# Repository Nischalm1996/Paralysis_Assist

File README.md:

# Paralysis_Assist

## Pin Connection from Board 
| Pin Name  | Digital Pin                            |
|-----------|----------------------------------------|
| CS_SDCARD | D2                                     |
| SOUND_D0  | D3  *Mic sensor from paralysed person* |
| AUDIO_OUT | D4 *to speaker*                        |
| MISO      | D5                                     |
| MOSI      | D10                                    |
| OK        | D6                                     |
| LEFT      | D7                                     |
| RIGHT     | D9                                     |
| BACK      | D8                                     |
| RIGHT     | D9                                     |
| CS_DISP   | D11                                    |
| RST       | D12                                    |
| TEMP      | A3                                     |
| RED       | A2                                     |
| GREEN     | A1                                     |
| BLUE      | A0                                     |

### MODULES USED
- DISPLAY 12864 SPI CONNECTOR
- NODE MCU
- MIC SENSOR
- MPU6050 ACCELOROMETER
- SD CARD
- LM35
- NAVIGATION BUTTON
- SOUND OUT----LM386
- RGB LED

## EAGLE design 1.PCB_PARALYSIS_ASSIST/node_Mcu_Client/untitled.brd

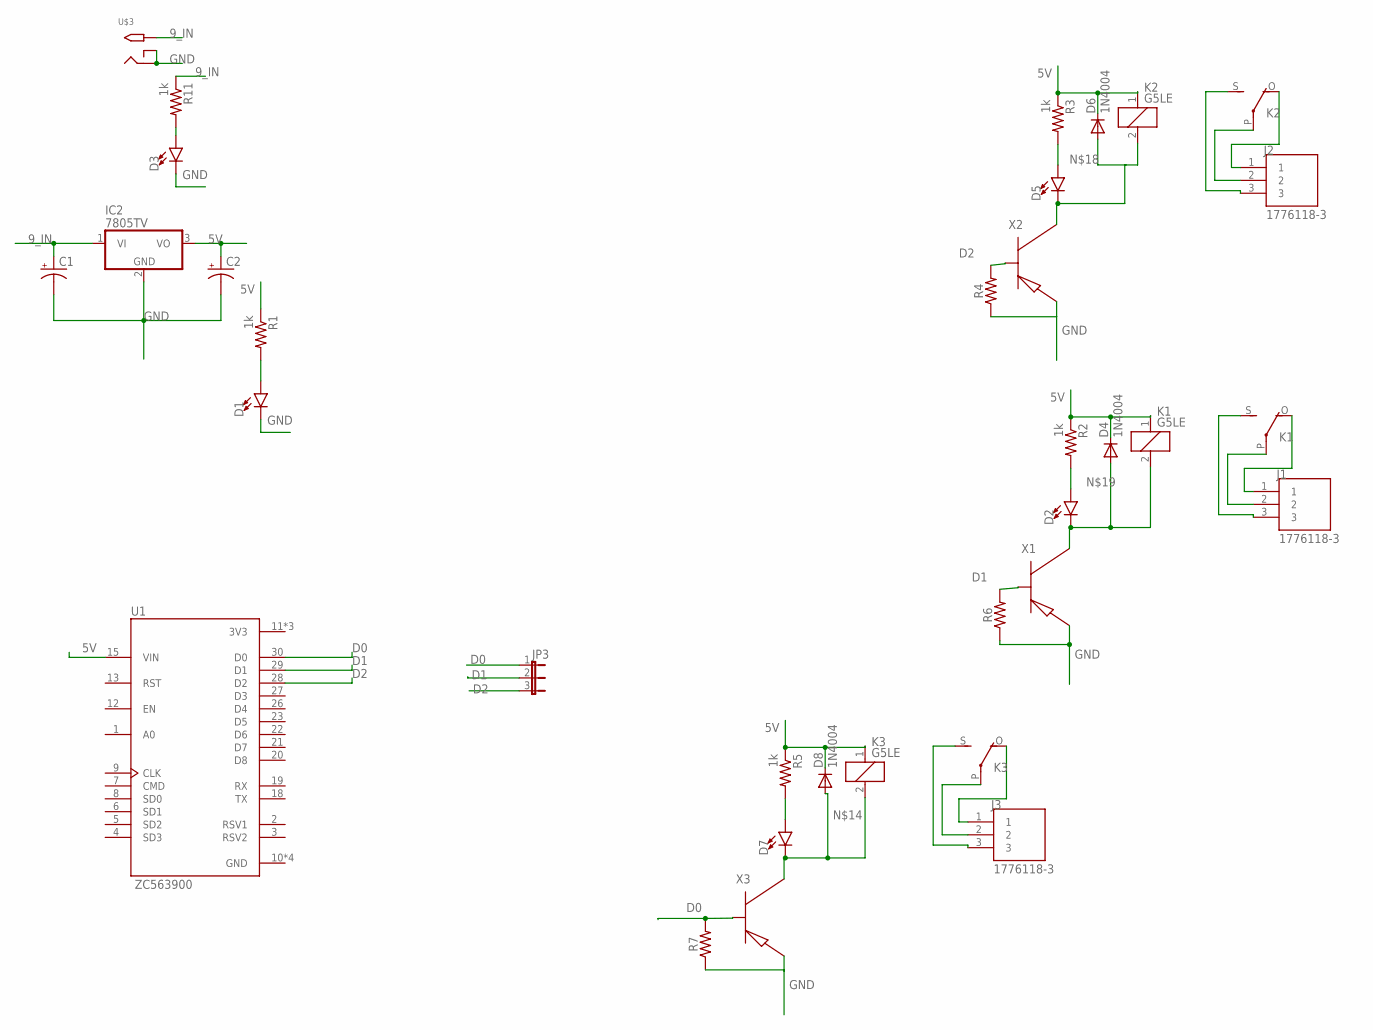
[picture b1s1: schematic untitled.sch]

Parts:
C1, C2: CPOL-USE3.5-8; E3,5-8
D1, D2, D3, D5, D7: LED3MM; LED_3MM
D4, D6, D8: 1N4004; DO41-10
IC2: 7805TV; TO220V
J1, J2, J3: 1776118-3; TE_1776118-3
JP3: JP2W
K1, K2, K3: G5LE
R1, R2, R3, R5, R11: 1k; M0805
R4, R6, R7: 330; M0805
U1: ZC563900; MODULE_ZC563900
U$3: 2.1MMJACKTHM; PJ-102A
X1, X2, X3: 2N3906; TO92

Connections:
3V3: U1.11 (3V3), U1.16 (3V3), U1.25 (3V3)
5V: C2.+, D4.C, D6.C, D8.C, IC2.3 (VO), K1.1, K2.1, K3.1, R1.1, R2.1, R3.1, R5.1, U1.15 (VIN)
9_IN: C1.+, IC2.1 (VI), R11.1, U$3.TIP
D0: JP3.1, R7.2, U1.30 (D0), X3.2 (B)
D1: JP3.2, R6.2, U1.29 (D1), X1.2 (B)
D2: JP3.3, R4.2, U1.28 (D2), X2.2 (B)
GND: C1.-, C2.-, D1.K (C), D3.K (C), IC2.2 (GND), R4.1, R6.1, R7.1, U1.10 (GND), U1.14 (GND), U1.17 (GND), U1.24 (GND), U$3.RING, U$3.RING_SW, X1.3 (E), X2.3 (E), X3.3 (E)
unnamed: D2.K (C), D4.A, K1.2, X1.1 (C)
unnamed: D3.A, R11.2
unnamed: D1.A, R1.2
unnamed: D7.A, R5.2
unnamed: J1.2, K1.P
unnamed: J1.1, K1.O
unnamed: J1.3, K1.S
unnamed: D5.K (C), D6.A, K2.2, X2.1 (C)
unnamed: J2.2, K2.P
unnamed: J2.1, K2.O
unnamed: J2.3, K2.S
unnamed: D7.K (C), D8.A, K3.2, X3.1 (C)
unnamed: J3.2, K3.P
unnamed: J3.1, K3.O
unnamed: J3.3, K3.S
unnamed: D5.A, R3.2
unnamed: D2.A, R2.2

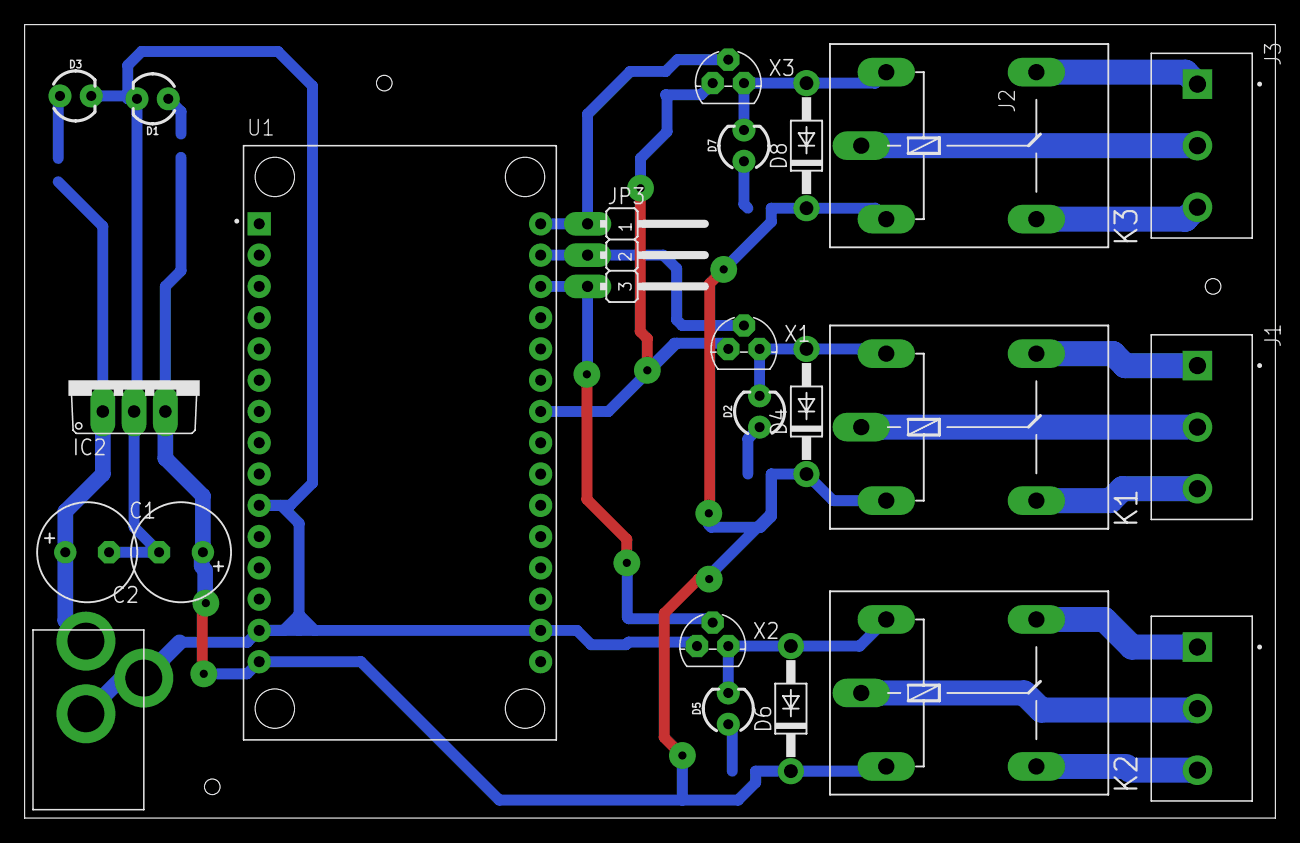
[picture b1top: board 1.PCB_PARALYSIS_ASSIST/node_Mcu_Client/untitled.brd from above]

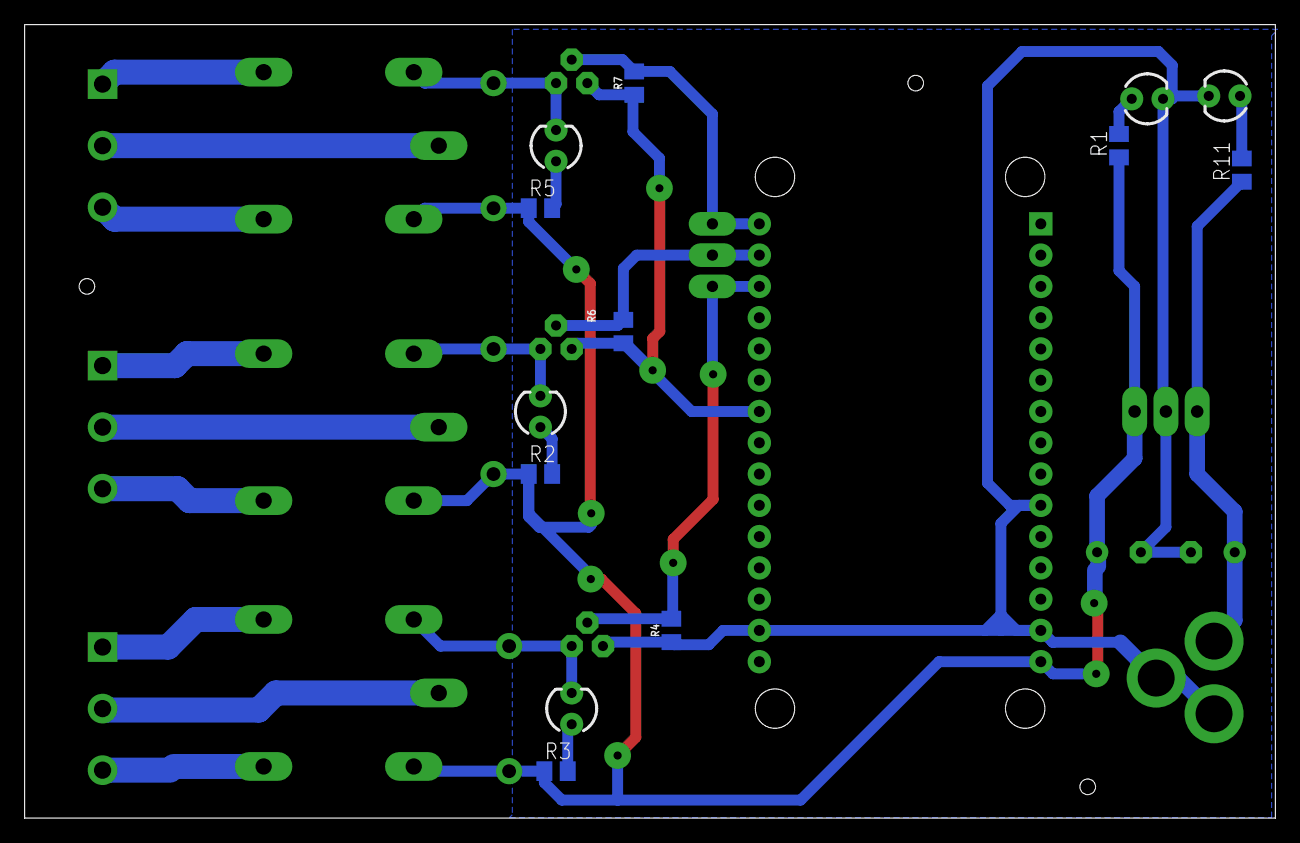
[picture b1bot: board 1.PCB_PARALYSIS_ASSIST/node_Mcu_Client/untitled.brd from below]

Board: 2 copper layers, 101.6 x 64.4 mm, 31 parts (8 on the bottom side), 24 nets.

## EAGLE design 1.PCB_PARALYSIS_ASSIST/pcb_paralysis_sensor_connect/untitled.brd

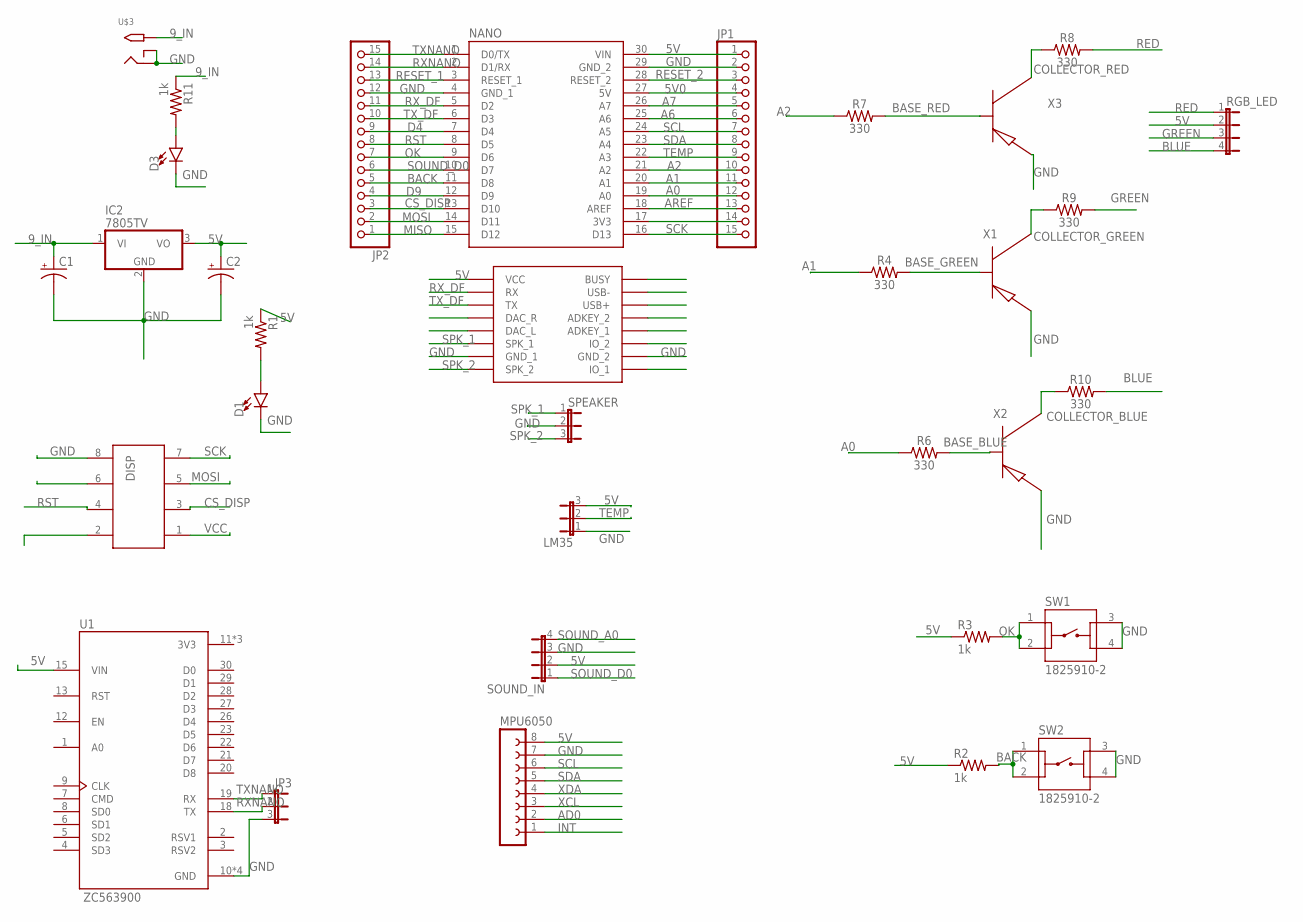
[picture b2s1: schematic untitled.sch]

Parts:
C1, C2: CPOL-USE3.5-8; E3,5-8
D1, D3: LED3MM; LED_3MM
DISP: 612008235121
IC2: 7805TV; TO220V
JP1, JP2: PINHD-1X15; 1X15
JP3: JP2W
LM35: JP2E; JP2
MPU6050: FE08-1; FE08
NANO: A000005; MODULE_A000005
R1, R2, R3, R11: 1k; M0805
R4, R6, R7, R8, R9, R10: 330; AXIAL-0.3
RGB_LED: JP4E; JP4
SOUND_IN: JP4E; JP4
SPEAKER: JP2E; JP2
SW1, SW2: 1825910-2; TE_1825910-2
U1: ZC563900; MODULE_ZC563900
U$1: DFPLAYER
U$3: 2.1MMJACKTHM; PJ-102A
X1, X2, X3: 2N3906; TO92

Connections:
3V3: U1.11 (3V3), U1.16 (3V3), U1.25 (3V3)
5V: C2.+, IC2.3 (VO), JP1.1, LM35.3, MPU6050.8, NANO.30 (VIN), R1.1, R2.1, R3.1, RGB_LED.2, SOUND_IN.2, U1.15 (VIN), U$1.VCC
5V0: JP1.4, NANO.27 (5V)
9_IN: C1.+, IC2.1 (VI), R11.1, U$3.TIP
A0: JP1.12, NANO.19 (A0), R6.P$1 (1)
A1: JP1.11, NANO.20 (A1), R4.P$1 (1)
A2: JP1.10, NANO.21 (A2), R7.P$1 (1)
A6: JP1.6, NANO.25 (A6)
A7: JP1.5, NANO.26 (A7)
AD0: MPU6050.2
AREF: JP1.13, NANO.18 (AREF)
BACK: JP2.5, NANO.11 (D8), R2.2, SW2.1, SW2.2
BASE_BLUE: R6.P$2 (2), X2.2 (B)
BASE_GREEN: R4.P$2 (2), X1.2 (B)
BASE_RED: R7.P$2 (2), X3.2 (B)
BLUE: R10.P$2 (2), RGB_LED.4
COLLECTOR_BLUE: R10.P$1 (1), X2.1 (C)
COLLECTOR_GREEN: R9.P$1 (1), X1.1 (C)
COLLECTOR_RED: R8.P$1 (1), X3.1 (C)
CS_DISP: DISP.3, JP2.3, NANO.13 (D10)
D4: JP2.9, NANO.7 (D4)
D9: JP2.4, NANO.12 (D9)
GND: C1.-, C2.-, D1.K (C), D3.K (C), DISP.8, IC2.2 (GND), JP1.2, JP2.12, JP3.3, LM35.1, MPU6050.7, NANO.4 (GND_1), NANO.29 (GND_2), SOUND_IN.3, SPEAKER.2, SW1.3, SW1.4, SW2.3, SW2.4, U1.10 (GND), U1.14 (GND), U1.17 (GND), U1.24 (GND), U$1.GND_1, U$1.GND_2, U$3.RING, U$3.RING_SW, X1.3 (E), X2.3 (E), X3.3 (E)
GREEN: R9.P$2 (2), RGB_LED.3
INT: MPU6050.1
MISO: JP2.1, NANO.15 (D12)
MOSI: DISP.5, JP2.2, NANO.14 (D11)
unnamed: D3.A, R11.2
unnamed: D1.A, R1.2
unnamed: JP1.14, NANO.17 (3V3)
OK: JP2.7, NANO.9 (D6), R3.2, SW1.1, SW1.2
RED: R8.P$2 (2), RGB_LED.1
RESET_1: JP2.13, NANO.3 (RESET_1)
RESET_2: JP1.3, NANO.28 (RESET_2)
RST: DISP.4, JP2.8, NANO.8 (D5)
RXNANO: JP2.14, JP3.2, NANO.2 (D1/RX), U1.18 (TX)
RX_DF: JP2.11, NANO.5 (D2), U$1.RX
SCK: DISP.7, JP1.15, NANO.16 (D13)
SCL: JP1.7, MPU6050.6, NANO.24 (A5)
SDA: JP1.8, MPU6050.5, NANO.23 (A4)
SOUND_A0: SOUND_IN.4
SOUND_D0: JP2.6, NANO.10 (D7), SOUND_IN.1
SPK_1: SPEAKER.1, U$1.SPK1 (SPK_1)
SPK_2: SPEAKER.3, U$1.SPK2 (SPK_2)
TEMP: JP1.9, LM35.2, NANO.22 (A3)
TXNANO: JP2.15, JP3.1, NANO.1 (D0/TX), U1.19 (RX)
TX_DF: JP2.10, NANO.6 (D3), U$1.TX
VCC: DISP.1
XCL: MPU6050.3
XDA: MPU6050.4

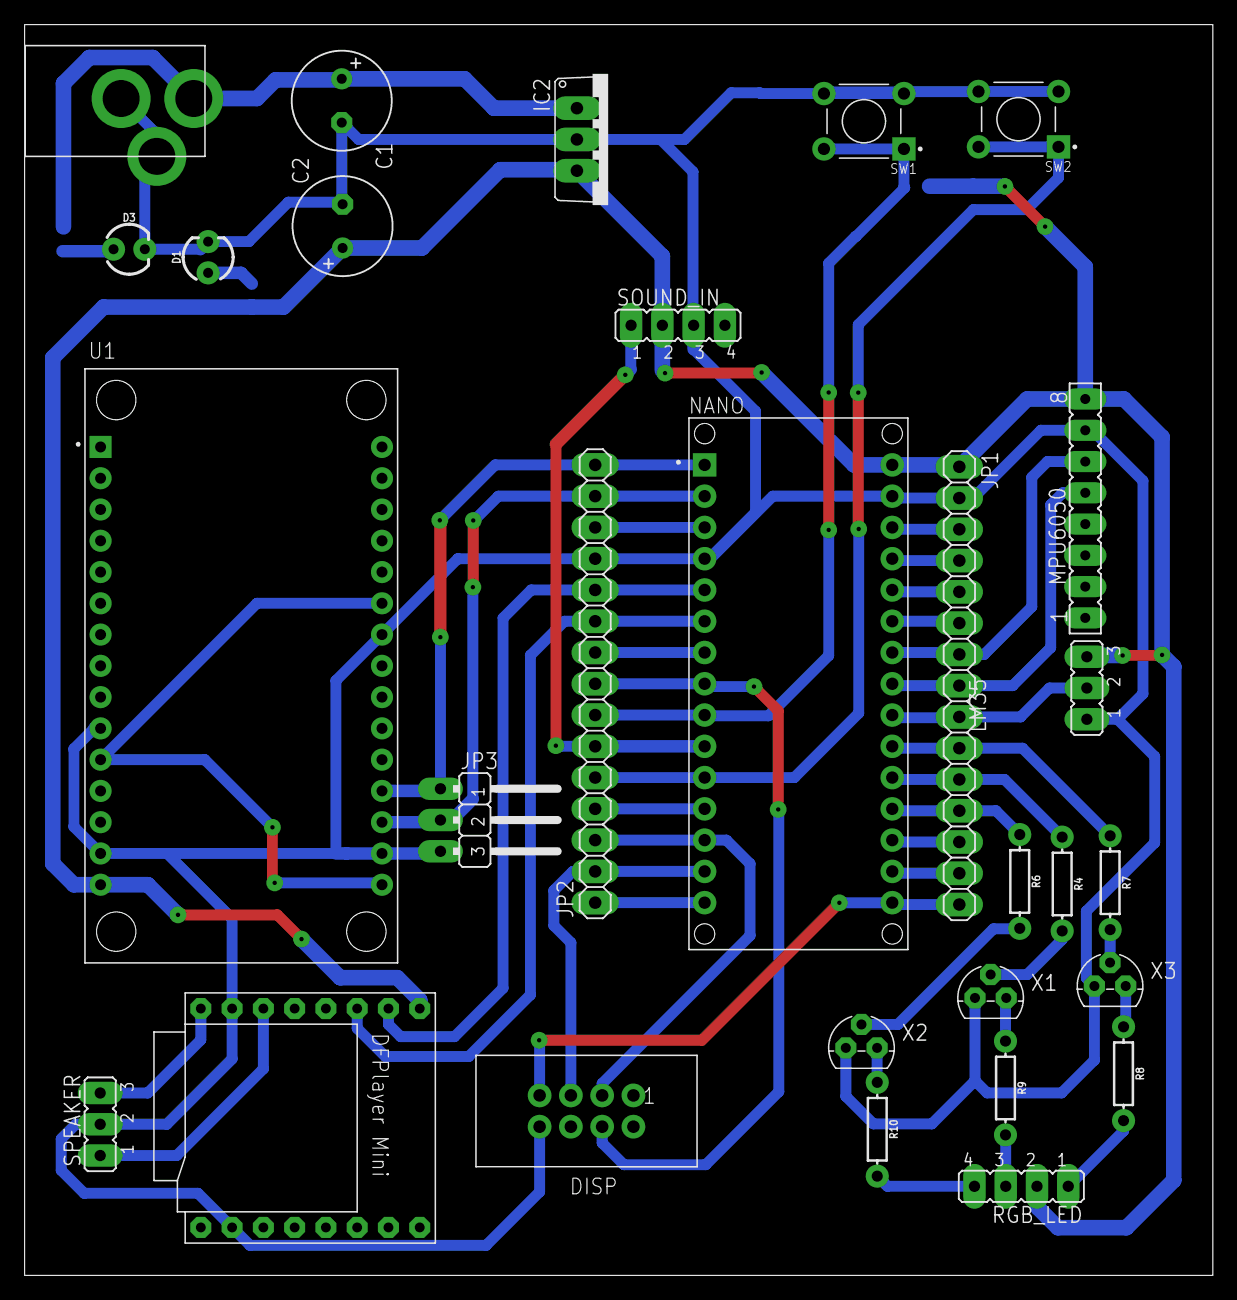
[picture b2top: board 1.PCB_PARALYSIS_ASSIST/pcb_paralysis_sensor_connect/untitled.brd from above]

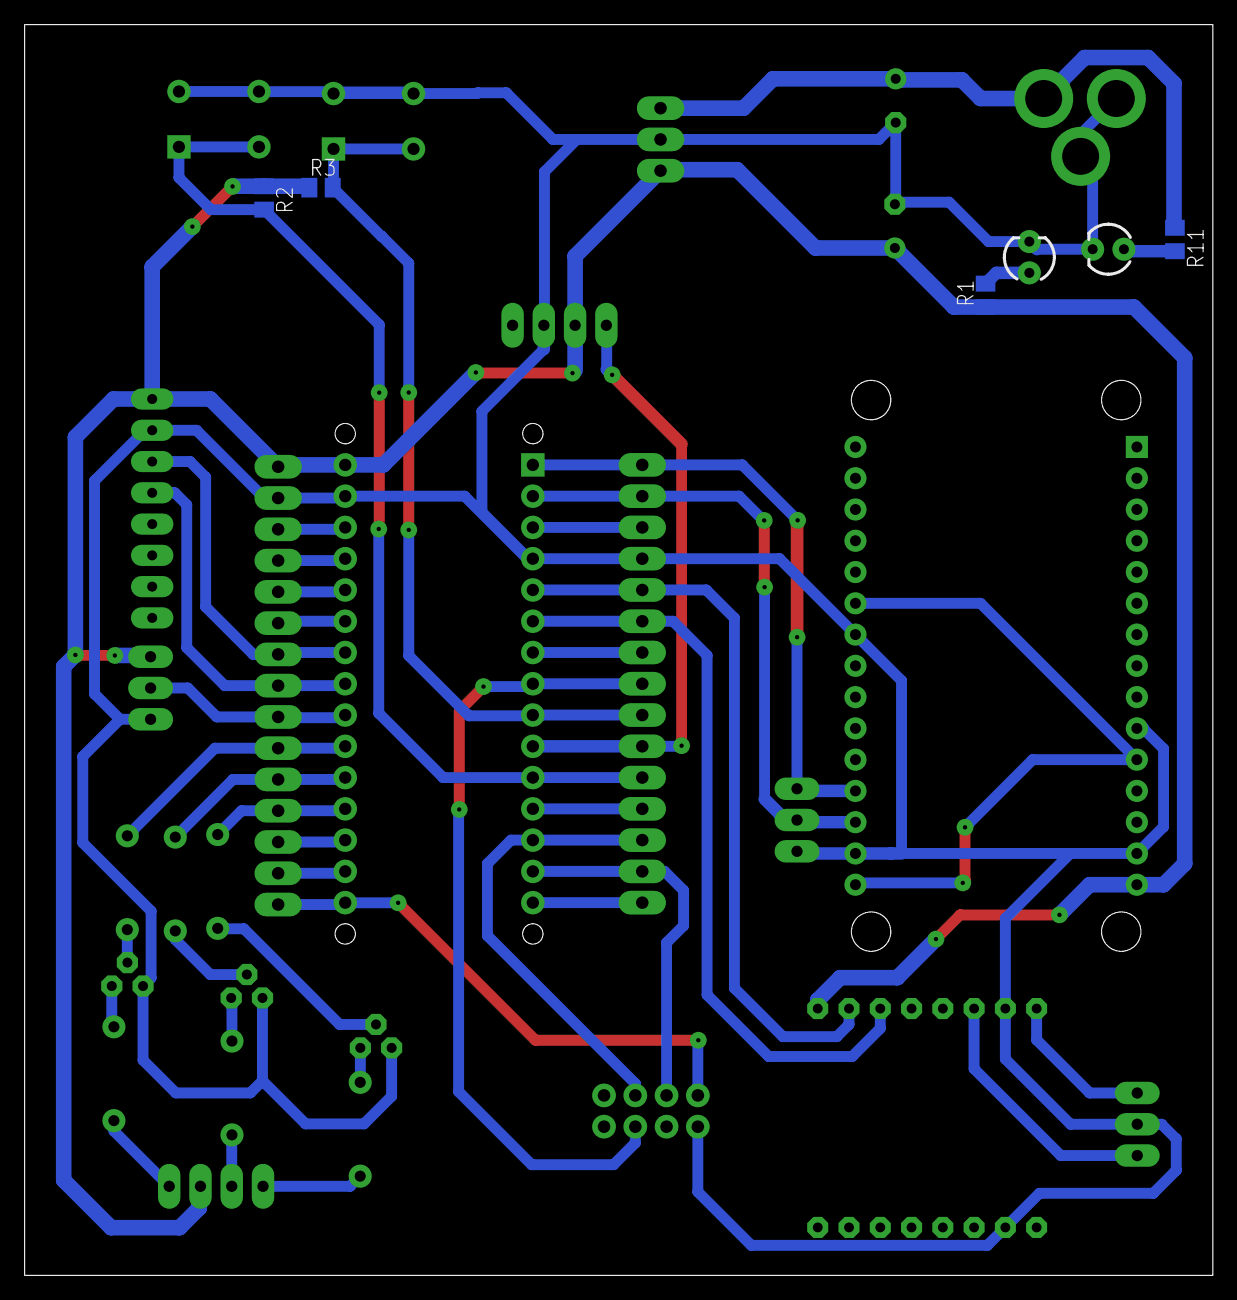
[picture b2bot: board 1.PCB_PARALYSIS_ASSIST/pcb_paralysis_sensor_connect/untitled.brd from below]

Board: 2 copper layers, 96.5 x 101.6 mm, 33 parts (4 on the bottom side), 44 nets.

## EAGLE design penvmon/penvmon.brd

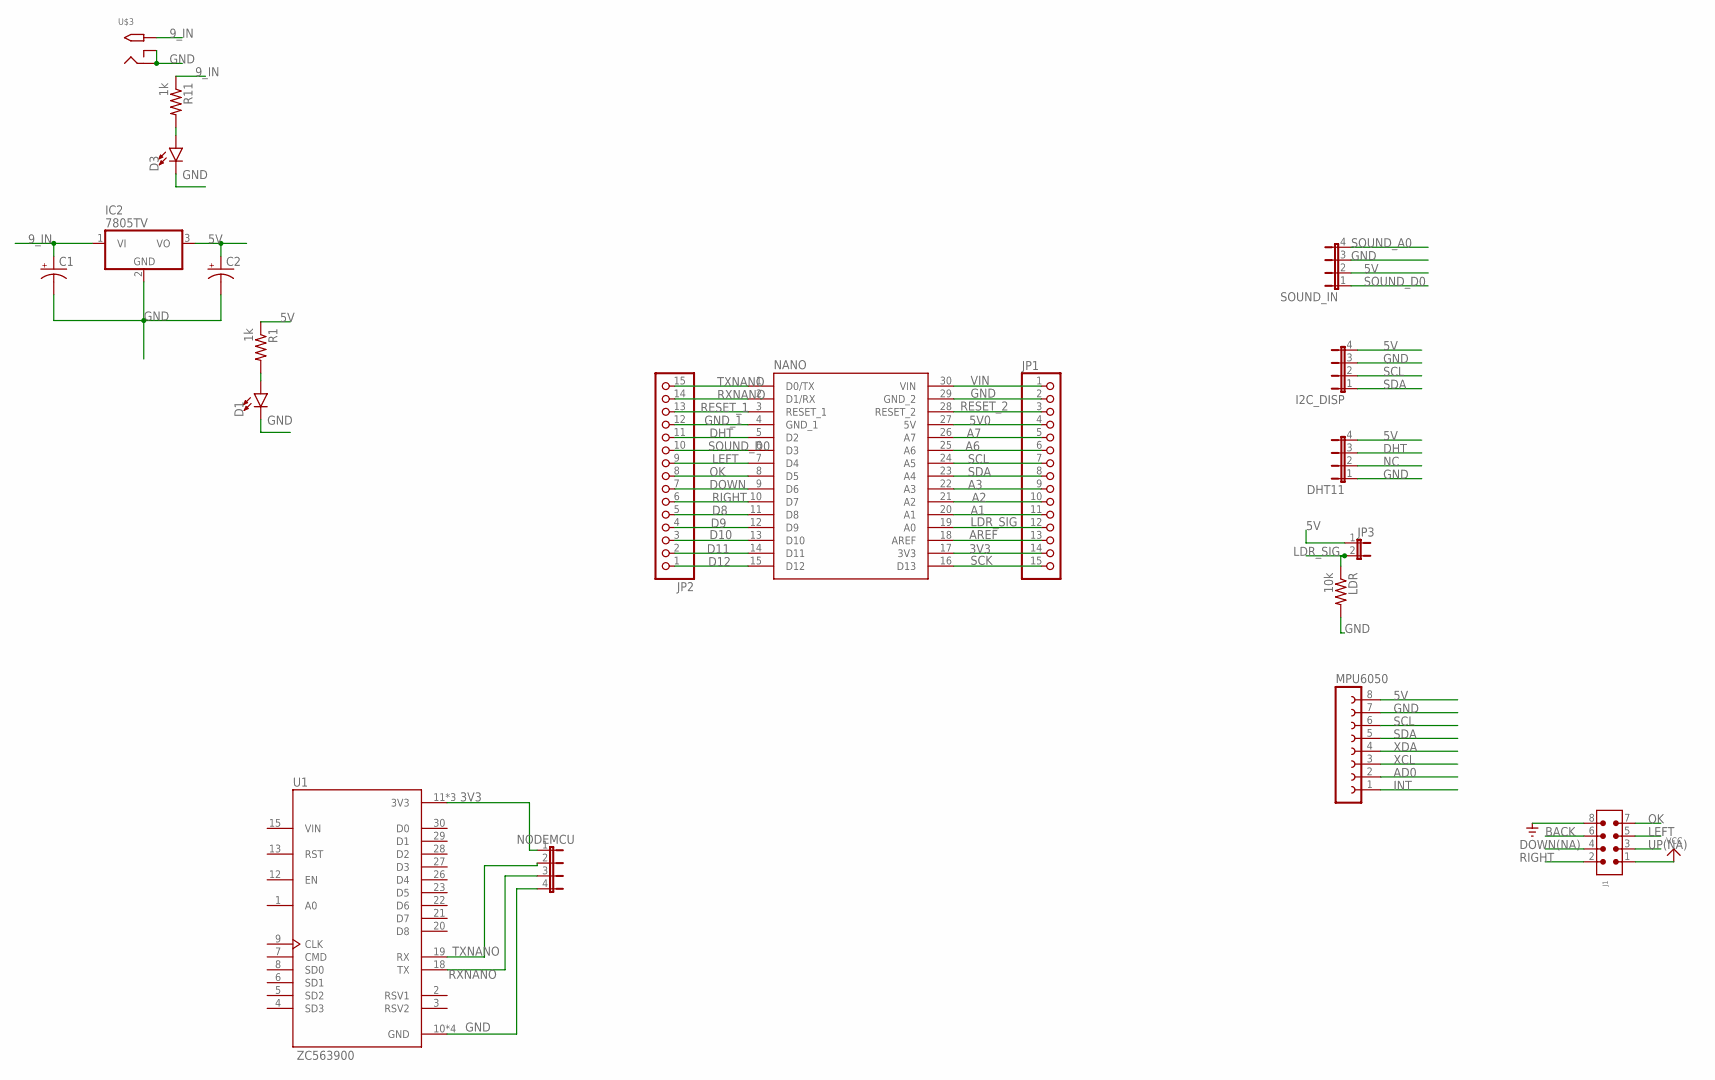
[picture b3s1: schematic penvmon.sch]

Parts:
C1, C2: CPOL-USE3.5-8; E3,5-8
D1, D3: LED3MM; LED_3MM
DHT11: JP4E; JP4
I2C_DISP: JP4E; JP4
IC2: 7805TV; TO220V
J1: 6120XX21621_61200821621; 61200821621
JP1, JP2: PINHD-1X15; 1X15
JP3: JP1E; JP1
LDR: 10k; M0805
MPU6050: FE08-1; FE08
NANO: A000005; MODULE_A000005
NODEMCU: JP4E; JP4
R1, R11: 1k; M0805
SOUND_IN: JP4E; JP4
U1: ZC563900; MODULE_ZC563900
U$3: 2.1MMJACKTHM; PJ-102A

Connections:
3V3: JP1.14, NANO.17 (3V3), NODEMCU.1, U1.11 (3V3), U1.16 (3V3), U1.25 (3V3)
5V: C2.+, DHT11.4, I2C_DISP.4, IC2.3 (VO), JP3.1, MPU6050.8, R1.1, SOUND_IN.2
5V0: JP1.4, NANO.27 (5V)
9_IN: C1.+, IC2.1 (VI), R11.1, U$3.TIP
A1: JP1.11, NANO.20 (A1)
A2: JP1.10, NANO.21 (A2)
A3: JP1.9, NANO.22 (A3)
A6: JP1.6, NANO.25 (A6)
A7: JP1.5, NANO.26 (A7)
AD0: MPU6050.2
AREF: JP1.13, NANO.18 (AREF)
BACK: J1.6
D8: JP2.5, NANO.11 (D8)
D9: JP2.4, NANO.12 (D9)
D10: JP2.3, NANO.13 (D10)
D11: JP2.2, NANO.14 (D11)
D12: JP2.1, NANO.15 (D12)
DHT: DHT11.3, JP2.11, NANO.5 (D2)
DOWN: JP2.7, NANO.9 (D6)
DOWN(NA): J1.4
GND: C1.-, C2.-, D1.K (C), D3.K (C), DHT11.1, I2C_DISP.3, IC2.2 (GND), J1.8, JP1.2, LDR.2, MPU6050.7, NANO.29 (GND_2), NODEMCU.4, SOUND_IN.3, U1.10 (GND), U1.14 (GND), U1.17 (GND), U1.24 (GND), U$3.RING, U$3.RING_SW
GND_1: JP2.12, NANO.4 (GND_1)
INT: MPU6050.1
LDR_SIG: JP1.12, JP3.2, LDR.1, NANO.19 (A0)
LEFT: J1.5, JP2.9, NANO.7 (D4)
unnamed: D3.A, R11.2
unnamed: D1.A, R1.2
NC: DHT11.2
OK: J1.7, JP2.8, NANO.8 (D5)
RESET_1: JP2.13, NANO.3 (RESET_1)
RESET_2: JP1.3, NANO.28 (RESET_2)
RIGHT: J1.2, JP2.6, NANO.10 (D7)
RXNANO: JP2.14, NANO.2 (D1/RX), NODEMCU.3, U1.18 (TX)
SCK: JP1.15, NANO.16 (D13)
SCL: I2C_DISP.2, JP1.7, MPU6050.6, NANO.24 (A5)
SDA: I2C_DISP.1, JP1.8, MPU6050.5, NANO.23 (A4)
SOUND_A0: SOUND_IN.4
SOUND_D0: JP2.10, NANO.6 (D3), SOUND_IN.1
TXNANO: JP2.15, NANO.1 (D0/TX), NODEMCU.2, U1.19 (RX)
UP(NA): J1.3
VCC: J1.1
VIN: JP1.1, NANO.30 (VIN)
XCL: MPU6050.3
XDA: MPU6050.4

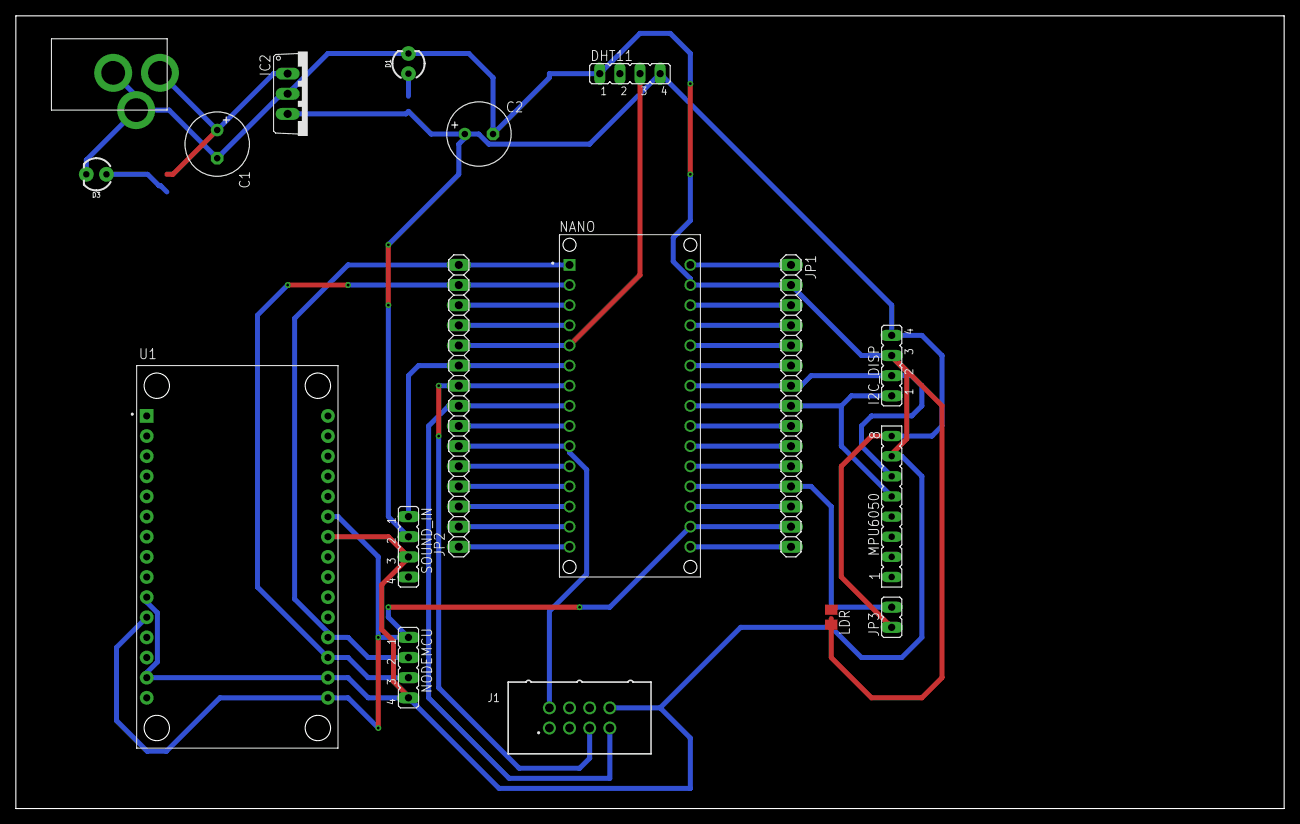
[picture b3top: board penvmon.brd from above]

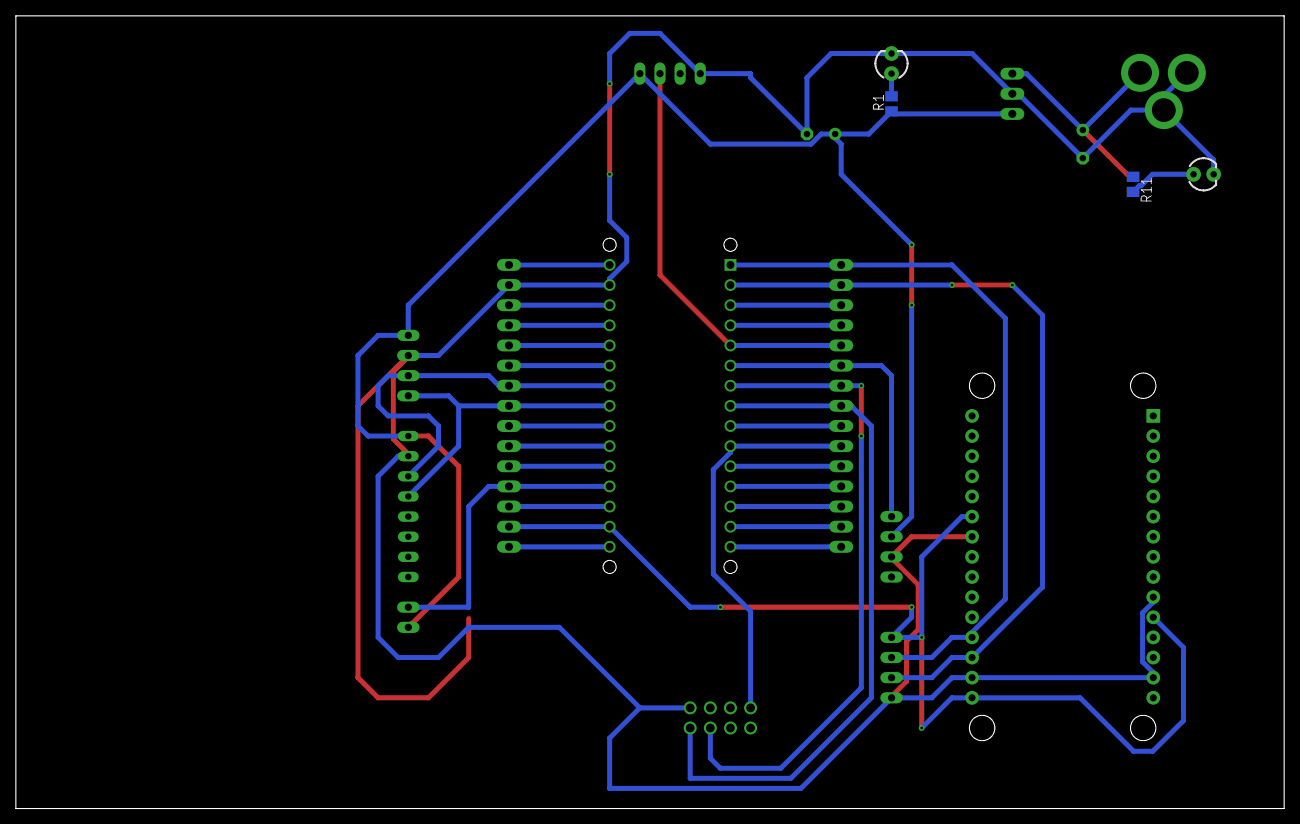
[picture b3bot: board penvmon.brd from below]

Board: 2 copper layers, 160.0 x 100.0 mm, 20 parts (2 on the bottom side), 34 nets.

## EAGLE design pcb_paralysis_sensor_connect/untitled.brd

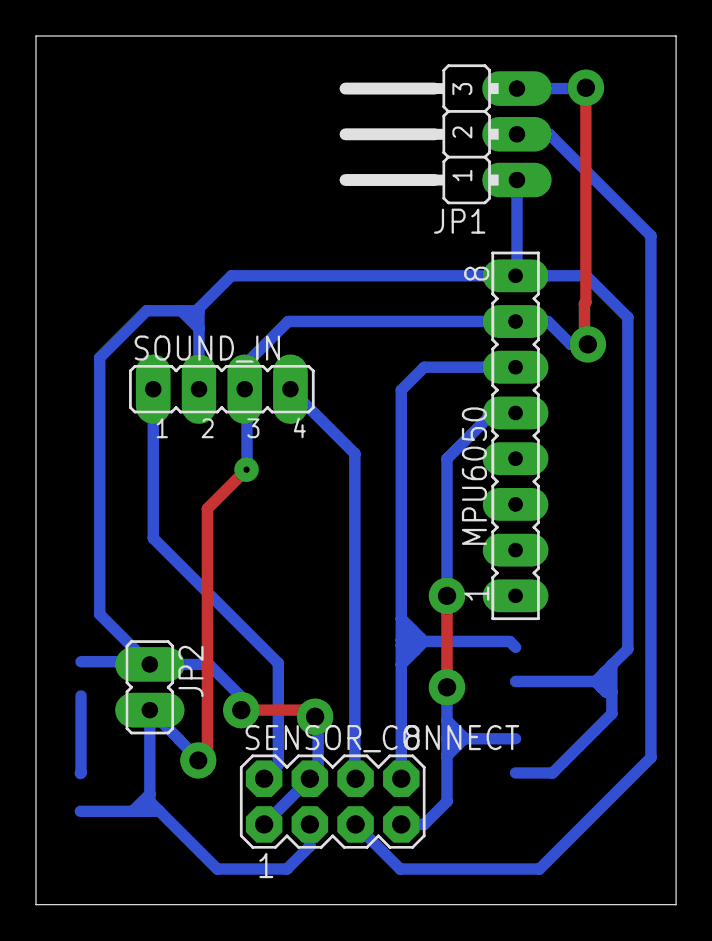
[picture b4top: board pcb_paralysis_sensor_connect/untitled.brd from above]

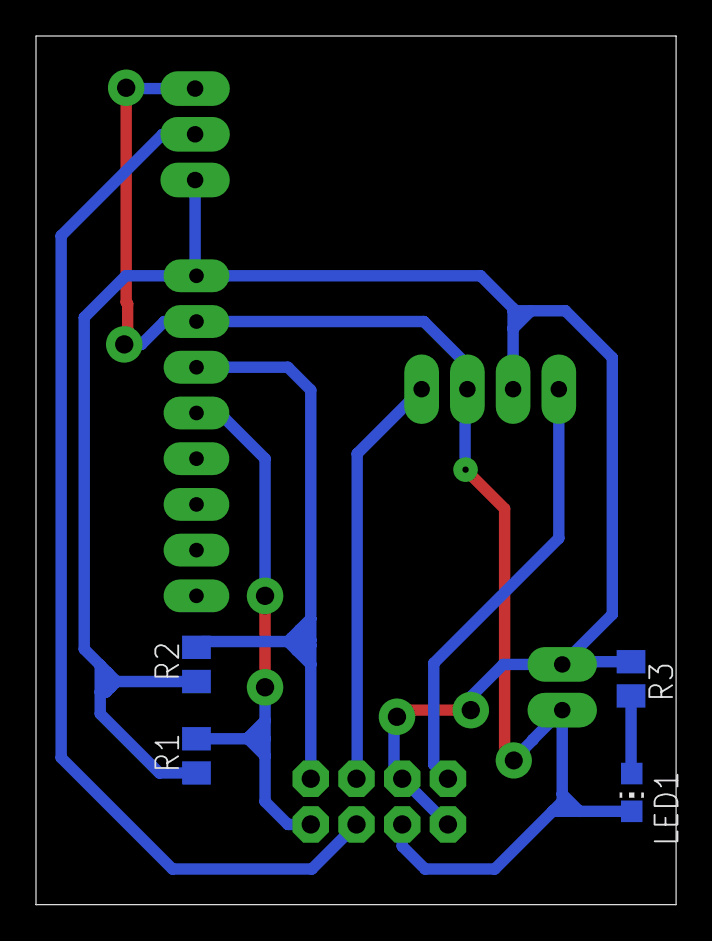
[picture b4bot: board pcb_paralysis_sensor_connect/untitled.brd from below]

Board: 2 copper layers, 35.6 x 48.3 mm, 9 parts (4 on the bottom side), 8 nets.

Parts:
JP1: JP2W
JP2: JP1
LED1: CHIP-LED0805
MPU6050: FE08
R1, R2, R3: 1k; M0805
SENSOR_CONNECT: MA04-2
SOUND_IN: JP4

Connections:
5V: JP1.1, JP2.1, MPU6050.8, R1.1, R2.1, R3.1, SENSOR_CONNECT.1, SENSOR_CONNECT.4, SOUND_IN.2
GND: JP1.3, JP2.2, LED1.C, MPU6050.7, SENSOR_CONNECT.3, SOUND_IN.3
unnamed: LED1.A, R3.2
SCL: MPU6050.6, R2.2, SENSOR_CONNECT.8
SDA: MPU6050.5, R1.2, SENSOR_CONNECT.7
SOUND_A0: SENSOR_CONNECT.6, SOUND_IN.4
SOUND_D0: SENSOR_CONNECT.2, SOUND_IN.1
TEMP_DATA: JP1.2, SENSOR_CONNECT.5

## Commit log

2021-02-22 initia commit of project
2021-02-22 Demonstation of change
2021-02-23 added lm35 temp sesnor header file
2021-03-15 initial_commit
2021-03-16 added image
2021-03-25 added Schematic
2021-03-25 updated readme with connections
2021-03-25 ADDED MODULES USED
2021-03-25 added initial files from students
2021-04-04 pcb_sensor_connect
    connecting the sensor in one pcb
2021-04-04 small board
2021-04-16 added schematics
2021-05-14 pcb changes
2021-05-15 pushing anjans code
2021-05-15 update sd speaker
2021-05-22 22may commit
2021-05-31 paralysis_version2 added pcb design
    design added
2021-05-31 updated version_2 layout
2021-06-02 corrections to the pcb
2021-06-02 version_2_corrected_copy
2021-06-02 added pcb
2021-06-08 image file edited for print
2021-06-09 added nodemcu_client and server
2021-06-11 hardware interface 1
2021-06-11 pagebuffer
2021-06-16 added Arduino Code
2021-06-16 lastest code with mpu6050 working
2021-06-20 directory structure changes
2021-06-20 Final Working with Audio issue fixed!
2021-06-20 Final_V2_NANO_CODE
2021-06-20 auxiliary server
2021-06-23 auxiliary_server
2021-06-23 controller and slave addeed
2021-06-23 delay removed
2021-06-23 working except twilio
2021-06-29 wtsapp_message_being_sent
2021-06-29 nodemcu pcb reciever added
2021-06-29 RGB led analog pin numbers added
2021-06-29 updated led functionality
2021-06-29 final nano
2021-06-29 updated pic of pcb
2021-07-02 controller corrected
2021-07-14 updated to narendras phone

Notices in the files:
parts and their libraries:
SparkFun-LED: Licensing: Creative Commons ShareAlike 4.0 International - https://creativecommons.org/licenses/by-sa/4.0
Wurth_Elektronik_Electromechanic_Wire_to: Copyright: Würth Elektronik
